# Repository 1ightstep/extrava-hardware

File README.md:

# Extrava Hardware

CAD, PCB, and firmware lives here.

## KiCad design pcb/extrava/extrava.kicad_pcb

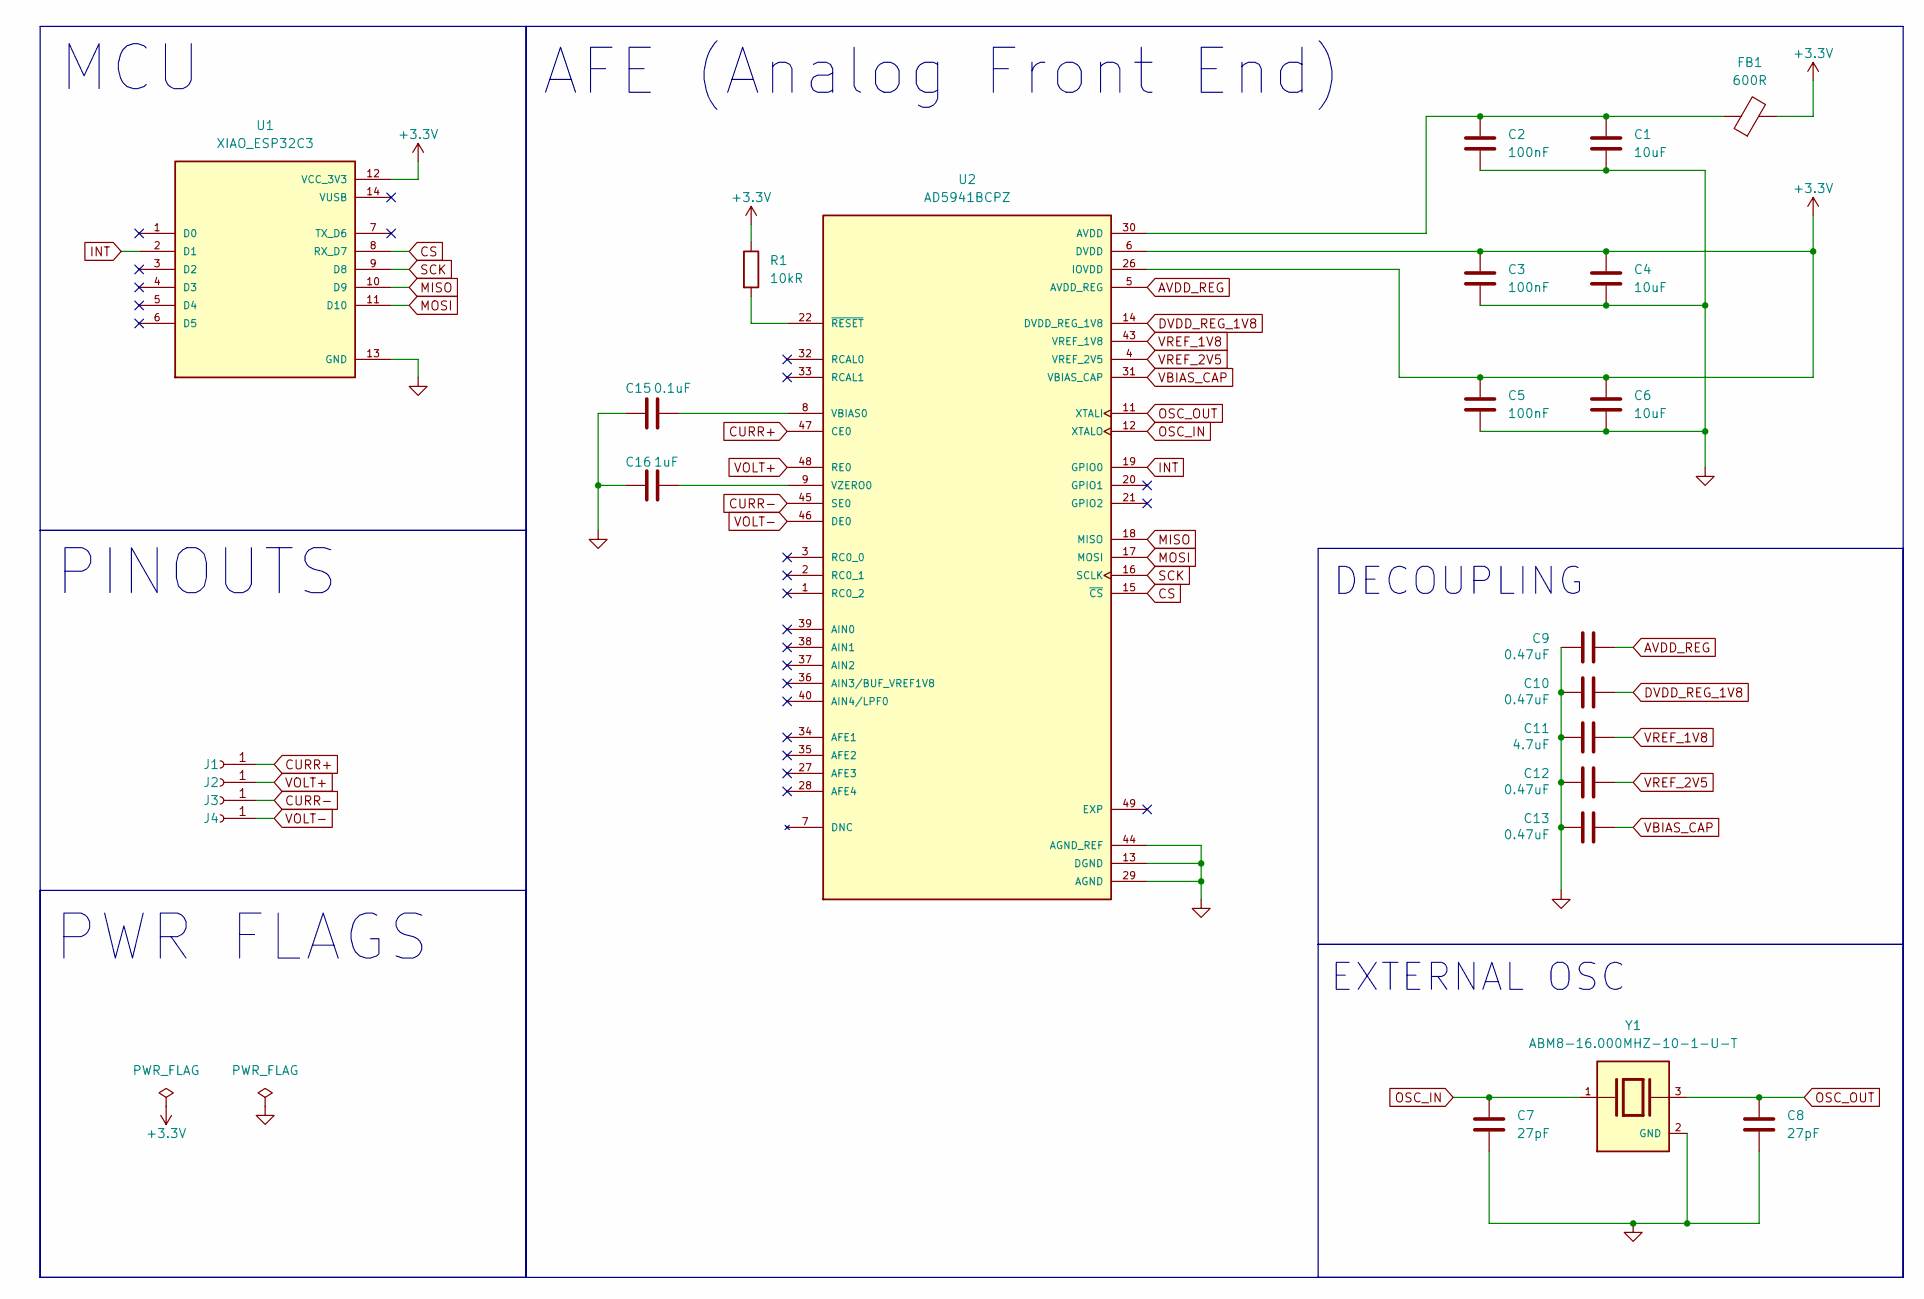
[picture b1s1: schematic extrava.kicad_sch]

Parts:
C1, C4, C6: 10uF; C_0603_1608Metric_Pad1.08x0.95mm_HandSolder
C2, C3, C5: 100nF; C_0603_1608Metric_Pad1.08x0.95mm_HandSolder
C7, C8: 27pF; C_0603_1608Metric_Pad1.08x0.95mm_HandSolder
C9, C10, C12, C13: 0.47uF; C_0603_1608Metric_Pad1.08x0.95mm_HandSolder
C11: 4.7uF; C_0603_1608Metric_Pad1.08x0.95mm_HandSolder
C15: 0.1uF; C_0603_1608Metric_Pad1.08x0.95mm_HandSolder
C16: 1uF; C_0603_1608Metric_Pad1.08x0.95mm_HandSolder
FB1: 600R; R_0603_1608Metric_Pad0.98x0.95mm_HandSolder
J1, J2, J3, J4: Conn_01x01_Socket; SolderWire-0.75sqmm_1x01_D1.25mm_OD3.5mm
R1: 10kR; R_0603_1608Metric_Pad0.98x0.95mm_HandSolder
U1: XIAO_ESP32C3; PARTREV 23/05/2022
U2: AD5941BCPZ; PARTREV B
Y1: ABM8-16.000MHZ-10-1-U-T; PARTREV 44041

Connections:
+3.3V: C3.1, C4.1, C5.1, C6.1, FB1.2, R1.1, U1.12 (VCC_3V3), U2.6 (DVDD), U2.26 (IOVDD)
AVDD: C1.1, C2.1, FB1.1, U2.30 (AVDD), U2.41 (AVDD)
AVDD_REG: C9.2, U2.5 (AVDD_REG)
CS: U1.8 (RX_D7), U2.15 (~CS)
CURR+: J1.1, U2.47 (CE0)
CURR-: J3.1, U2.45 (SE0)
DVDD_REG_1V8: C10.2, U2.14 (DVDD_REG_1V8)
GND: C1.2, C2.2, C3.2, C4.2, C5.2, C6.2, C7.2, C8.2, C9.1, C10.1, C11.1, C12.1, C13.1, C15.1, C16.1, U1.13 (GND), U2.13 (DGND), U2.23 (DGND), U2.25 (DGND), U2.29 (AGND), U2.39 (AIN0), U2.42 (AGND), U2.44 (AGND_REF), Y1.2 (GND), Y1.4 (GND); also elsewhere on the board
INT: U1.2 (D1), U2.19 (GPIO0)
MISO: U1.10 (D9), U2.18 (MISO)
MOSI: U1.11 (D10), U2.17 (MOSI)
unnamed: C15.2, U2.8 (VBIAS0)
unnamed: C16.2, U2.9 (VZERO0)
unnamed: R1.2, U2.22 (~RESET)
OSC_IN: C7.1, U2.12 (XTALO), Y1.1
OSC_OUT: C8.1, U2.11 (XTALI), Y1.3
SCK: U1.9 (D8), U2.16 (SCLK)
VBIAS_CAP: C13.2, U2.31 (VBIAS_CAP)
VELOSTAT+: U2.20 (GPIO1); also elsewhere on the board
VOLT+: J2.1, U2.48 (RE0)
VOLT-: J4.1, U2.46 (DE0)
VREF_1V8: C11.2, U2.43 (VREF_1V8)
VREF_2V5: C12.2, U2.4 (VREF_2V5)

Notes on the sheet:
DECOUPLING
AFE (Analog Front End)
PWR FLAGS
PINOUTS
MCU
EXTERNAL OSC

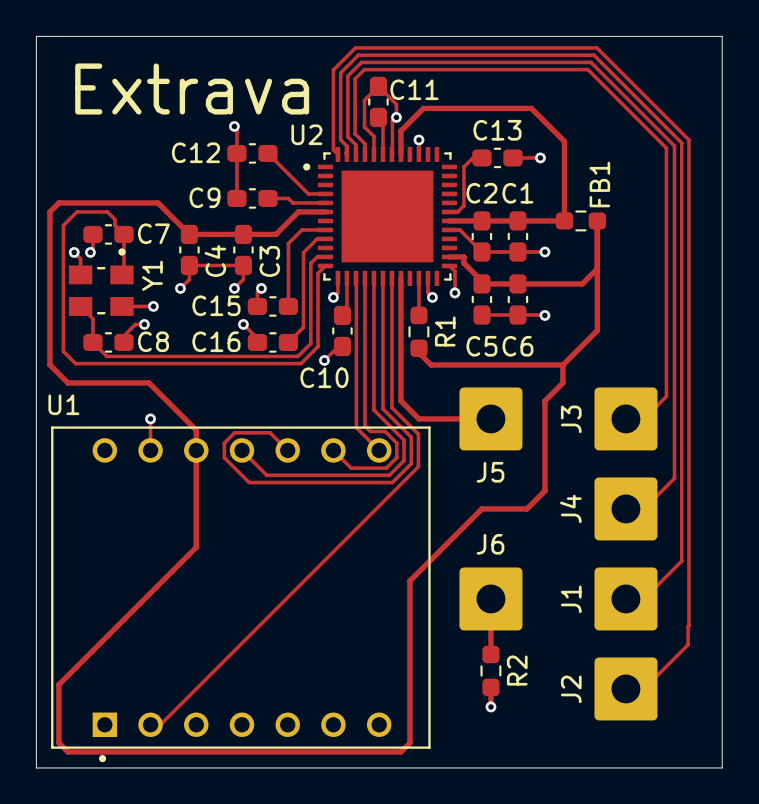
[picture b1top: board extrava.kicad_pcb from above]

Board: 2 copper layers, 38.1 x 40.6 mm, 27 parts (0 on the bottom side), 24 nets.

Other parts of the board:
J5, J6: Conn_01x01_Socket; SolderWire-0.75sqmm_1x01_D1.25mm_OD3.5mm
R2: 10kR; R_0603_1608Metric_Pad0.98x0.95mm_HandSolder

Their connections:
GND: R2.2; also elsewhere on the board
VELOSTAT+: J5.1; also elsewhere on the board
VELOSTAT-: J6.1, R2.1

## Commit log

2026-06-09 docs: initial commit
2026-06-11 feat: pcb schematics + layout finished, gerbers generated
2026-06-16 fix(layout): closer decoupling caps
2026-06-24 feat: added velostat to system
2026-06-24 chore: tiddy wire traces
